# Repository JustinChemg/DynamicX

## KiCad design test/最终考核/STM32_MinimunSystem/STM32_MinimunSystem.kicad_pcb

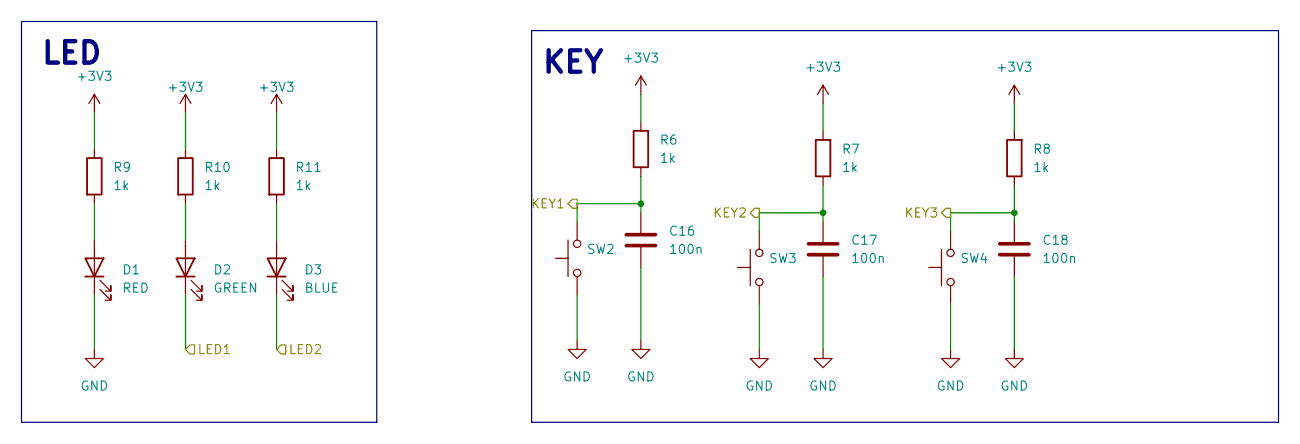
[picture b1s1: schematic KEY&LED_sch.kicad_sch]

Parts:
C16, C17, C18: 100n; C_0603_1608Metric
D1: RED; LED_0201_0603Metric
D2: GREEN; LED_0201_0603Metric
D3: BLUE; LED_0201_0603Metric
R6, R7, R8, R9, R10, R11: 1k; R_0603_1608Metric
SW2, SW3, SW4: SW_Push; SW_Push_1P1T_NO_6x6mm_H9.5mm

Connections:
+3V3: R6.2, R7.2, R8.2, R9.1, R10.1, R11.1; also elsewhere on the board
/STM32_MinimumSystem/PA15: D2.1 (K); also elsewhere on the board
/STM32_MinimumSystem/PB3: D3.1 (K); also elsewhere on the board
/STM32_MinimumSystem/PB4: C18.1, R8.1, SW4.2; also elsewhere on the board
/STM32_MinimumSystem/PB8: C17.1, R7.1, SW3.2; also elsewhere on the board
/STM32_MinimumSystem/PB9: C16.1, R6.1, SW2.2; also elsewhere on the board
GND: C16.2, C17.2, C18.2, D1.1 (K), SW2.1, SW3.1, SW4.1; also elsewhere on the board
unnamed: D1.2 (A), R9.2
unnamed: D2.2 (A), R10.2
unnamed: D3.2 (A), R11.2

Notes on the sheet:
KEY
LED

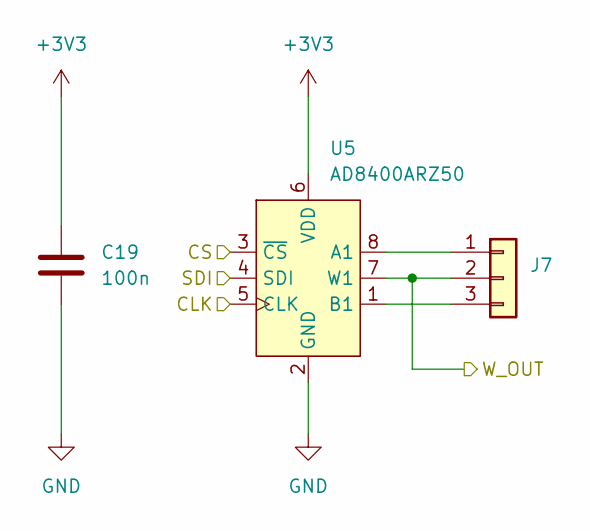
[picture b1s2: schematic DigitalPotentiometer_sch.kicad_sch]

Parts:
C19: 100n; C_0603_1608Metric
J7: Conn_01x03; PinHeader_1x03_P2.54mm_Vertical
U5: AD8400ARZ50; SOP-8_3.9x4.9mm_P1.27mm

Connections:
+3V3: C19.1, U5.6 (VDD); also elsewhere on the board
/STM32_MinimumSystem/PA0: J7.2, U5.7 (W1); also elsewhere on the board
/STM32_MinimumSystem/PA4: U5.3 (~CS); also elsewhere on the board
/STM32_MinimumSystem/PA5: U5.4 (SDI); also elsewhere on the board
/STM32_MinimumSystem/PA7: U5.5 (CLK); also elsewhere on the board
GND: C19.2, U5.2 (GND); also elsewhere on the board
unnamed: J7.1, U5.8 (A1)
unnamed: J7.3, U5.1 (B1)

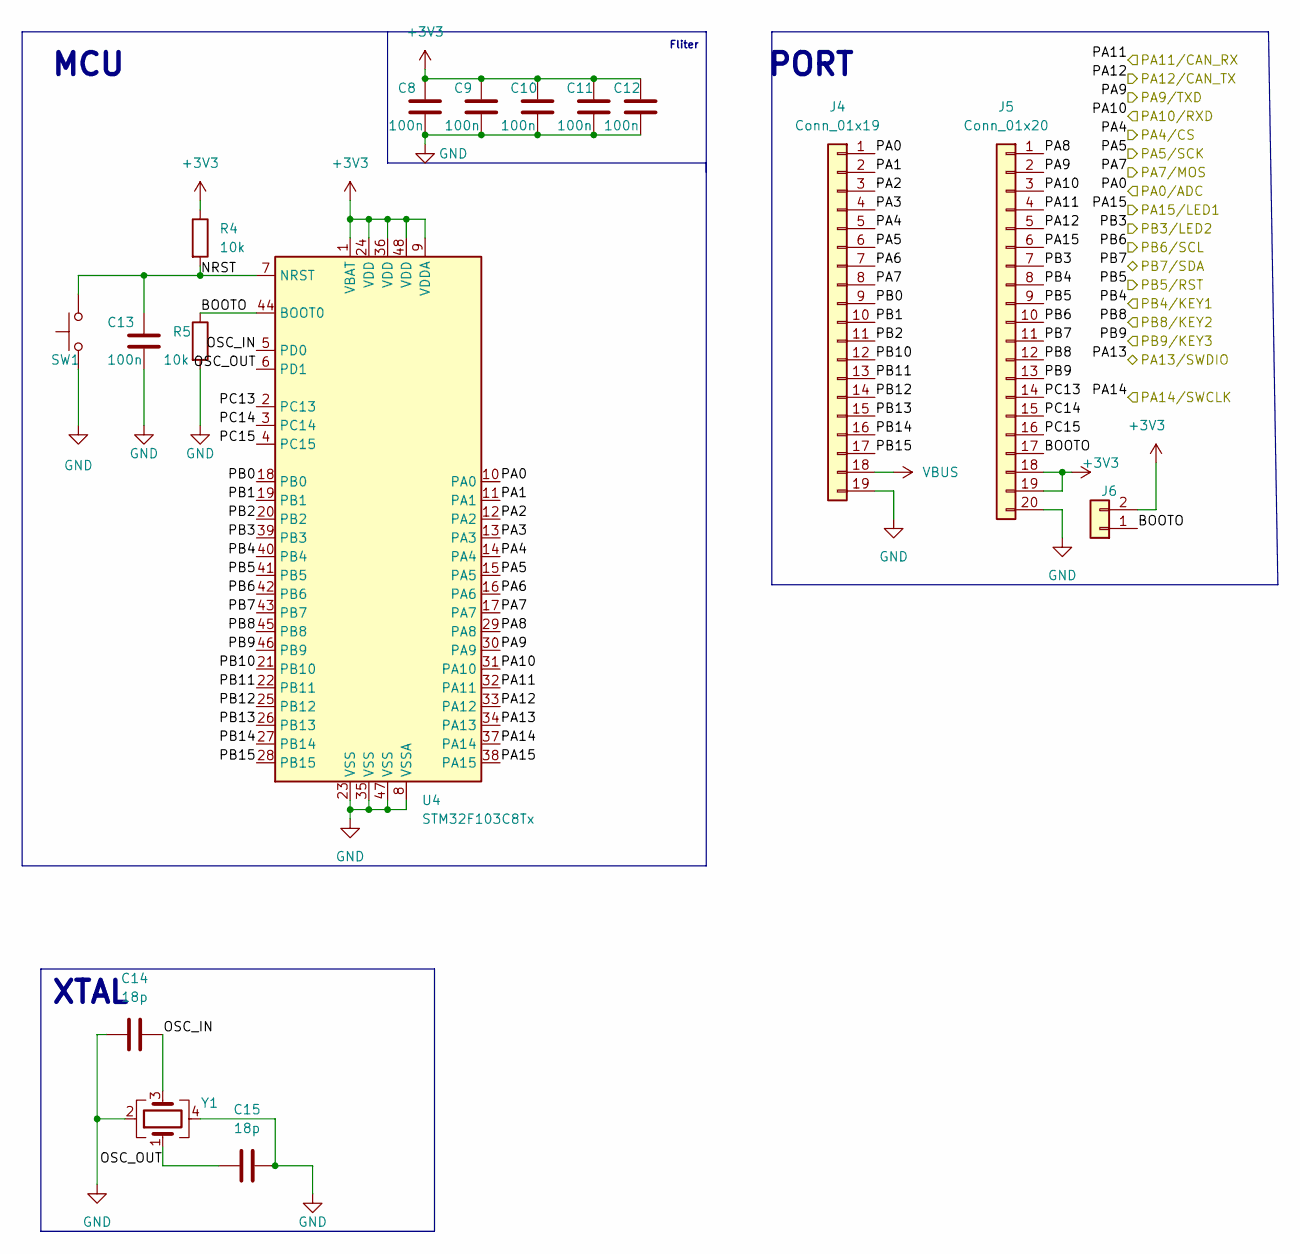
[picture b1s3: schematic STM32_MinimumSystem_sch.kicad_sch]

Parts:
C8, C9, C10, C11, C12, C13: 100n; C_0603_1608Metric
C14, C15: 18p; C_0603_1608Metric
J4: Conn_01x19; PinHeader_1x19_P2.54mm_Vertical
J5: Conn_01x20; PinHeader_1x20_P2.54mm_Vertical
J6: Conn_01x02; PinHeader_1x02_P2.54mm_Vertical
R4, R5: 10k; R_0603_1608Metric
SW1: SW_Push; SW_Push_1P1T_NO_6x6mm_H9.5mm
U4: STM32F103C8Tx; LQFP-48_7x7mm_P0.5mm
Y1: Crystal_GND24; Crystal_SMD_3225-4Pin_3.2x2.5mm

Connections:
+3V3: C8.1, C9.1, C10.1, C11.1, C12.1, J5.18, J5.19, J6.2, R4.1, U4.1 (VBAT), U4.9 (VDDA), U4.24 (VDD), U4.36 (VDD), U4.48 (VDD); also elsewhere on the board
/STM32_MinimumSystem/BOOTO: J5.17, J6.1, R5.1, U4.44 (BOOT0)
/STM32_MinimumSystem/NRST: C13.1, R4.2, SW1.2, U4.7 (NRST)
/STM32_MinimumSystem/OSC_IN: C14.2, U4.5 (PD0), Y1.3
/STM32_MinimumSystem/OSC_OUT: C15.1, U4.6 (PD1), Y1.1
/STM32_MinimumSystem/PA0: J4.1, U4.10 (PA0); also elsewhere on the board
/STM32_MinimumSystem/PA1: J4.2, U4.11 (PA1)
/STM32_MinimumSystem/PA2: J4.3, U4.12 (PA2)
/STM32_MinimumSystem/PA3: J4.4, U4.13 (PA3)
/STM32_MinimumSystem/PA4: J4.5, U4.14 (PA4); also elsewhere on the board
/STM32_MinimumSystem/PA5: J4.6, U4.15 (PA5); also elsewhere on the board
/STM32_MinimumSystem/PA6: J4.7, U4.16 (PA6)
/STM32_MinimumSystem/PA7: J4.8, U4.17 (PA7); also elsewhere on the board
/STM32_MinimumSystem/PA8: J5.1, U4.29 (PA8)
/STM32_MinimumSystem/PA9: J5.2, U4.30 (PA9); also elsewhere on the board
/STM32_MinimumSystem/PA10: J5.3, U4.31 (PA10); also elsewhere on the board
/STM32_MinimumSystem/PA11: J5.4, U4.32 (PA11); also elsewhere on the board
/STM32_MinimumSystem/PA12: J5.5, U4.33 (PA12); also elsewhere on the board
/STM32_MinimumSystem/PA13: U4.34 (PA13); also elsewhere on the board
/STM32_MinimumSystem/PA14: U4.37 (PA14); also elsewhere on the board
/STM32_MinimumSystem/PA15: J5.6, U4.38 (PA15); also elsewhere on the board
/STM32_MinimumSystem/PB0: J4.9, U4.18 (PB0)
/STM32_MinimumSystem/PB1: J4.10, U4.19 (PB1)
/STM32_MinimumSystem/PB2: J4.11, U4.20 (PB2)
/STM32_MinimumSystem/PB3: J5.7, U4.39 (PB3); also elsewhere on the board
/STM32_MinimumSystem/PB4: J5.8, U4.40 (PB4); also elsewhere on the board
/STM32_MinimumSystem/PB5: J5.9, U4.41 (PB5)
/STM32_MinimumSystem/PB6: J5.10, U4.42 (PB6)
/STM32_MinimumSystem/PB7: J5.11, U4.43 (PB7)
/STM32_MinimumSystem/PB8: J5.12, U4.45 (PB8); also elsewhere on the board
/STM32_MinimumSystem/PB9: J5.13, U4.46 (PB9); also elsewhere on the board
/STM32_MinimumSystem/PB10: J4.12, U4.21 (PB10)
/STM32_MinimumSystem/PB11: J4.13, U4.22 (PB11)
/STM32_MinimumSystem/PB12: J4.14, U4.25 (PB12)
/STM32_MinimumSystem/PB13: J4.15, U4.26 (PB13)
/STM32_MinimumSystem/PB14: J4.16, U4.27 (PB14)
/STM32_MinimumSystem/PB15: J4.17, U4.28 (PB15)
/STM32_MinimumSystem/PC13: J5.14, U4.2 (PC13)
/STM32_MinimumSystem/PC14: J5.15, U4.3 (PC14)
/STM32_MinimumSystem/PC15: J5.16, U4.4 (PC15)
GND: C8.2, C9.2, C10.2, C11.2, C12.2, C13.2, C14.1, C15.2, J4.19, J5.20, R5.2, SW1.1, U4.8 (VSSA), U4.23 (VSS), U4.35 (VSS), U4.47 (VSS), Y1.2, Y1.4; also elsewhere on the board
VBUS: J4.18; also elsewhere on the board

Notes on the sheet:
Fliter
XTAL
MCU
PORT

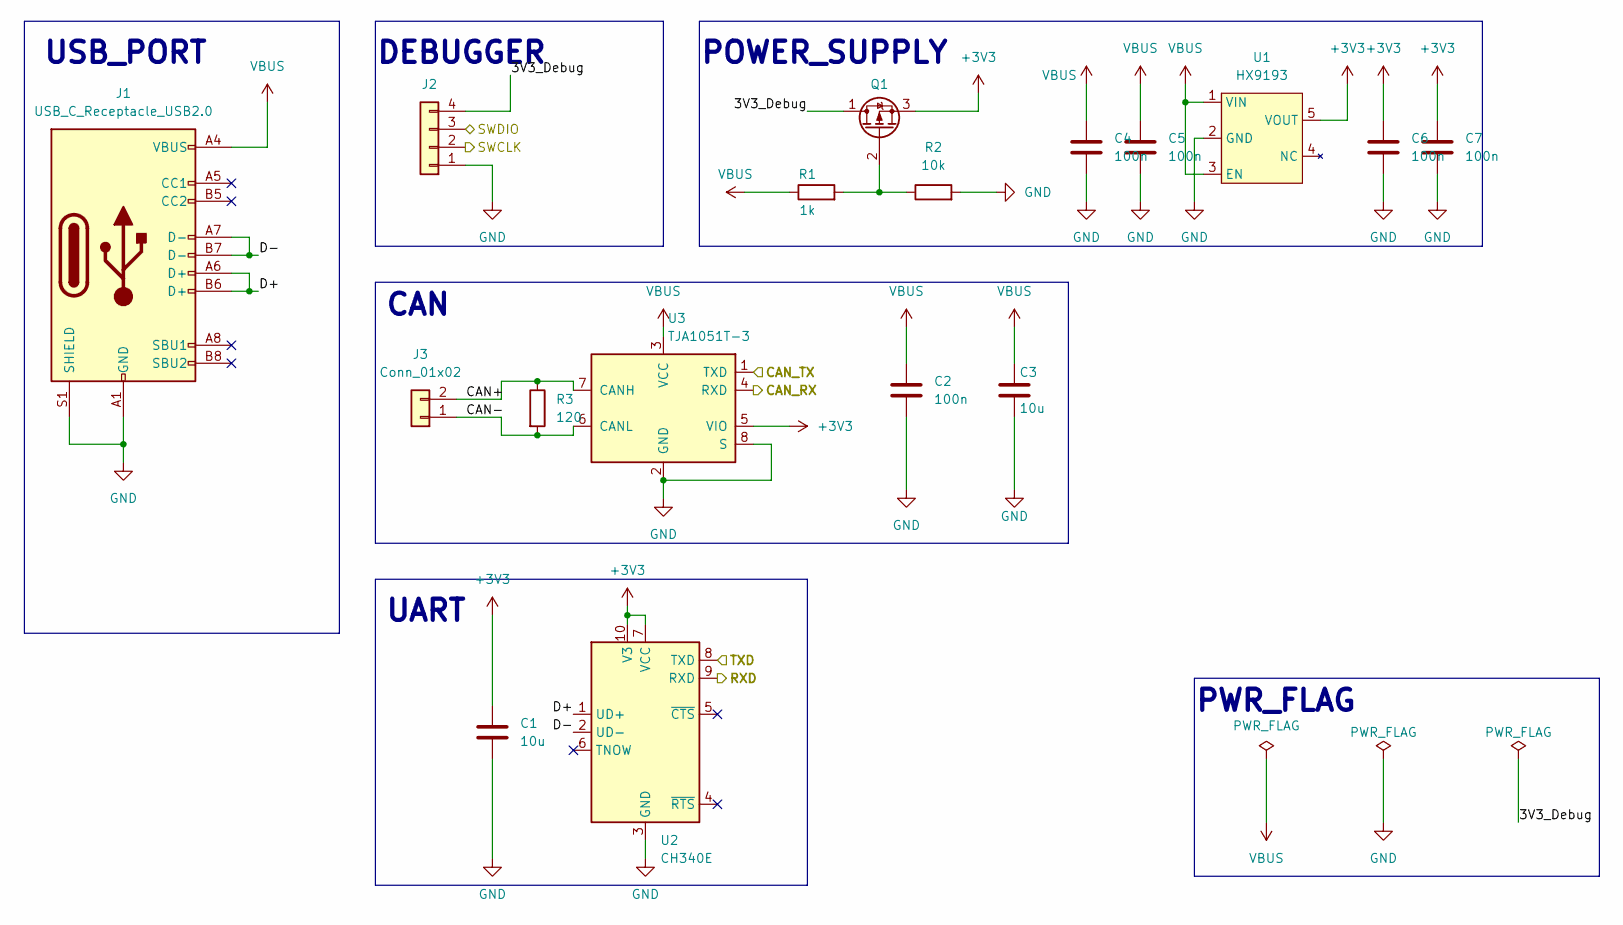
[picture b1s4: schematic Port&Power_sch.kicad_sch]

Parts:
C1, C3: 10u; C_0603_1608Metric
C2, C4, C5, C6, C7: 100n; C_0603_1608Metric
J1: USB_C_Receptacle_USB2.0; USB_C_Receptacle_Palconn_UTC16-G
J2: Conn_01x04; PinHeader_1x04_P2.54mm_Vertical
J3: Conn_01x02; JST_GH_SM02B-GHS-TB_1x02-1MP_P1.25mm_Horizontal
Q1: Q_PMOS_DGS; TSOT-23
R1: 1k; R_0603_1608Metric
R2: 10k; R_0603_1608Metric
R3: 120; R_0603_1608Metric
U1: HX9193; SOT-23-5_HandSoldering
U2: CH340E; MSOP-10_3x3mm_P0.5mm
U3: TJA1051T-3; SOIC-8_3.9x4.9mm_P1.27mm

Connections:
+3V3: C1.1, C6.1, C7.1, Q1.3 (S), U1.5 (VOUT), U2.7 (VCC), U2.10 (V3), U3.5 (VIO); also elsewhere on the board
/Port&Power/3V3_Debug: J2.4, Q1.1 (D)
/Port&Power/CAN+: J3.2, R3.1, U3.7 (CANH)
/Port&Power/CAN-: J3.1, R3.2, U3.6 (CANL)
/Port&Power/D+: J1.A6 (D+), J1.B6 (D+), U2.1 (UD+)
/Port&Power/D-: J1.A7 (D-), J1.B7 (D-), U2.2 (UD-)
/STM32_MinimumSystem/PA9: U2.8 (TXD); also elsewhere on the board
/STM32_MinimumSystem/PA10: U2.9 (RXD); also elsewhere on the board
/STM32_MinimumSystem/PA11: U3.4 (RXD); also elsewhere on the board
/STM32_MinimumSystem/PA12: U3.1 (TXD); also elsewhere on the board
/STM32_MinimumSystem/PA13: J2.3; also elsewhere on the board
/STM32_MinimumSystem/PA14: J2.2; also elsewhere on the board
GND: C1.2, C2.2, C3.2, C4.2, C5.2, C6.2, C7.2, J1.A1 (GND), J1.A12 (GND), J1.B1 (GND), J1.B12 (GND), J1.S1 (SHIELD), J2.1, R2.2, U1.2 (GND), U2.3 (GND), U3.2 (GND), U3.8 (S); also elsewhere on the board
unnamed: Q1.2 (G), R1.2, R2.1
VBUS: C2.1, C3.1, C4.1, C5.1, J1.A4 (VBUS), J1.A9 (VBUS), J1.B4 (VBUS), J1.B9 (VBUS), R1.1, U1.1 (VIN), U1.3 (EN), U3.3 (VCC); also elsewhere on the board

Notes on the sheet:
PWR_FLAG
UART
POWER_SUPPLY
CAN
DEBUGGER
USB_PORT

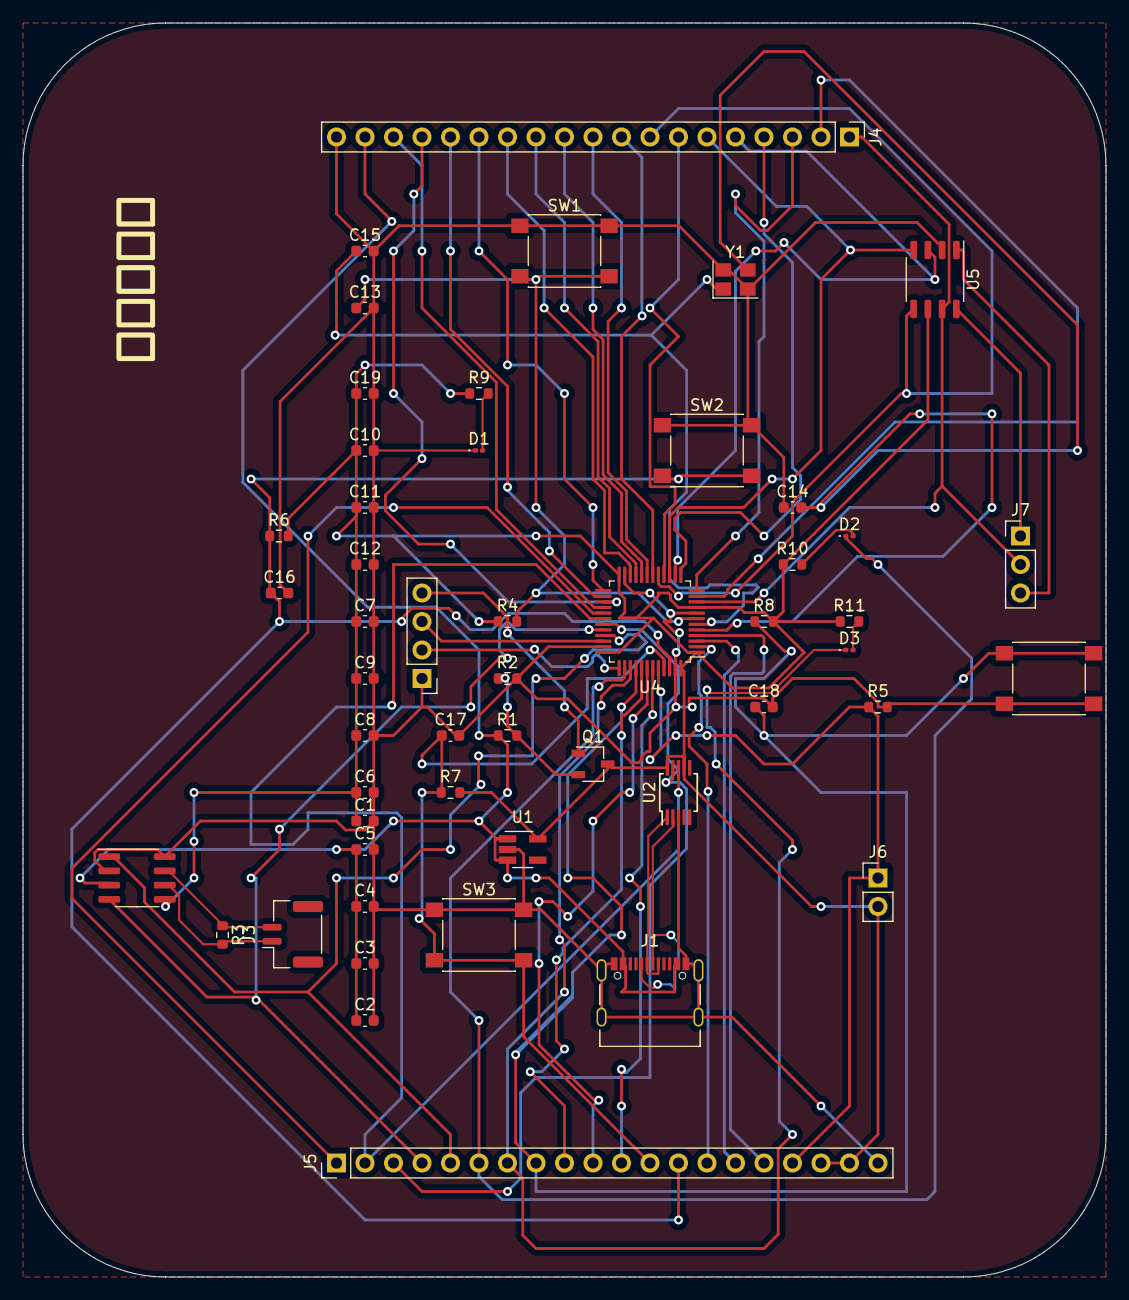
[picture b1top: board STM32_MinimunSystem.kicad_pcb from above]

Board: 2 copper layers, 96.5 x 111.8 mm, 51 parts (0 on the bottom side), 53 nets.

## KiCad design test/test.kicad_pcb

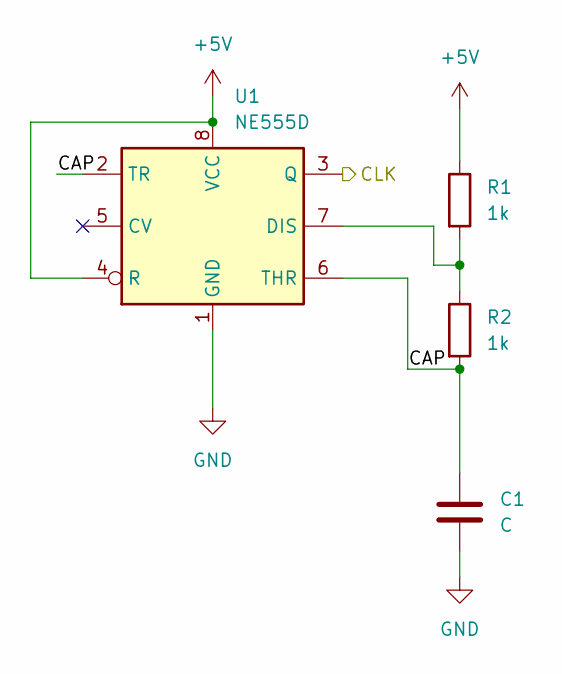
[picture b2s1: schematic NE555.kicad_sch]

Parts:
C1: C; C_0603_1608Metric
R1, R2: 1k; R_0201_0603Metric
U1: NE555D; SOIC-8_3.9x4.9mm_P1.27mm

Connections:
+5V: R1.1, U1.4 (R), U1.8 (VCC); also elsewhere on the board
/4017/CLK: U1.3 (Q); also elsewhere on the board
/NE555/CAP: C1.1, R2.2, U1.2 (TR), U1.6 (THR)
GND: C1.2, U1.1 (GND); also elsewhere on the board
unnamed: R1.2, R2.1, U1.7 (DIS)

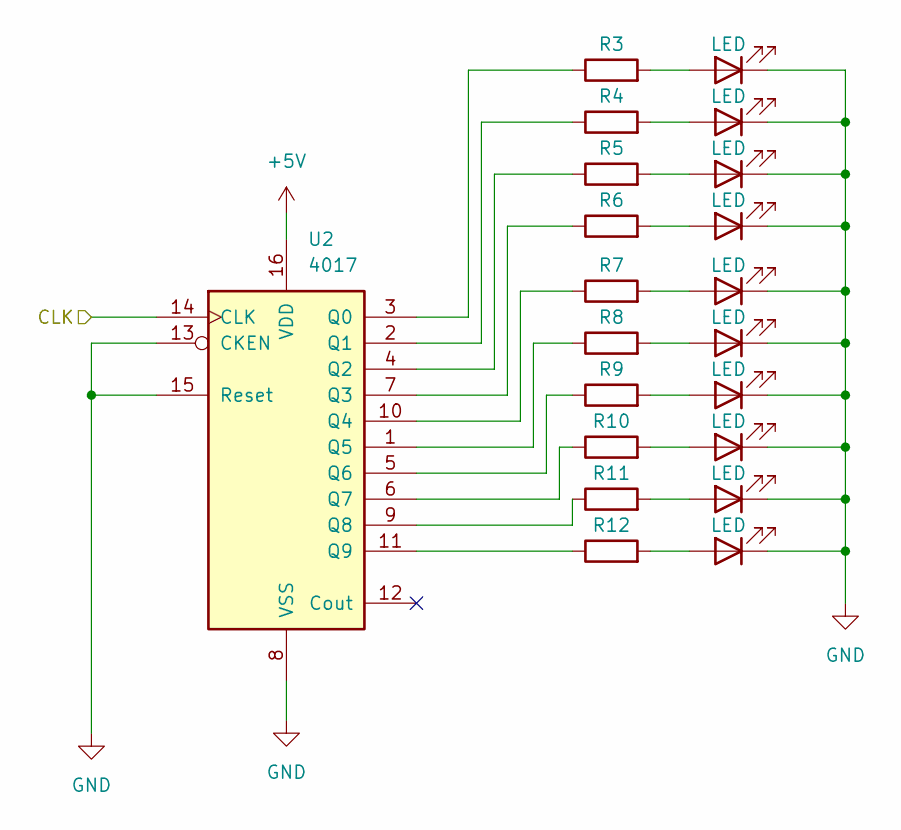
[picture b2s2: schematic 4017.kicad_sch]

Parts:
D1, D2, D3, D4, D5, D6, D7, D8, D9, D10: LED; LED_0603_1608Metric
R3, R4, R5, R6, R7, R8, R9, R10, R11, R12: 300; R_0201_0603Metric
U2: 4017; DIP-16_W7.62mm

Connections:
+5V: U2.16 (VDD); also elsewhere on the board
/4017/CLK: U2.14 (CLK); also elsewhere on the board
GND: D1.1 (K), D2.1 (K), D3.1 (K), D4.1 (K), D5.1 (K), D6.1 (K), D7.1 (K), D8.1 (K), D9.1 (K), D10.1 (K), U2.8 (VSS), U2.13 (CKEN), U2.15 (Reset); also elsewhere on the board
unnamed: D1.2 (A), R3.2
unnamed: D2.2 (A), R4.2
unnamed: D3.2 (A), R5.2
unnamed: D4.2 (A), R6.2
unnamed: D5.2 (A), R7.2
unnamed: D6.2 (A), R8.2
unnamed: D7.2 (A), R9.2
unnamed: D8.2 (A), R10.2
unnamed: D9.2 (A), R11.2
unnamed: D10.2 (A), R12.2
unnamed: R3.1, U2.3 (Q0)
unnamed: R4.1, U2.2 (Q1)
unnamed: R5.1, U2.4 (Q2)
unnamed: R6.1, U2.7 (Q3)
unnamed: R7.1, U2.10 (Q4)
unnamed: R8.1, U2.1 (Q5)
unnamed: R9.1, U2.5 (Q6)
unnamed: R10.1, U2.6 (Q7)
unnamed: R11.1, U2.9 (Q8)
unnamed: R12.1, U2.11 (Q9)

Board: 2 copper layers, 26 parts (0 on the bottom side), 25 nets, no tracks yet.

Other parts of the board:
J?: Conn_01x02; PinHeader_1x02_P2.54mm_Horizontal

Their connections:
+5V: J?.2; also elsewhere on the board
GND: J?.1; also elsewhere on the board

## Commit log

2022-10-02 practise
2022-10-03 test
2022-10-03 test2
2022-10-03 test3
